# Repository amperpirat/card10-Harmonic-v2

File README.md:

# card10-Harmonic-v2
This is an alternative Harmonic Board for the card10 design.

# Hardware

KiCad version 5.0 or newer is required, 5.1 is recommended.

If you are reading this, you are likely also wondering how to get access to push to this repo.
Currently the repo is read-only, please get in touch directly
via Matrix ( #card10badge:asra.gr ) or IRC ( freenode.com#card10badge, mirror)
if you want to contribute to the hardware.

## Known Issues

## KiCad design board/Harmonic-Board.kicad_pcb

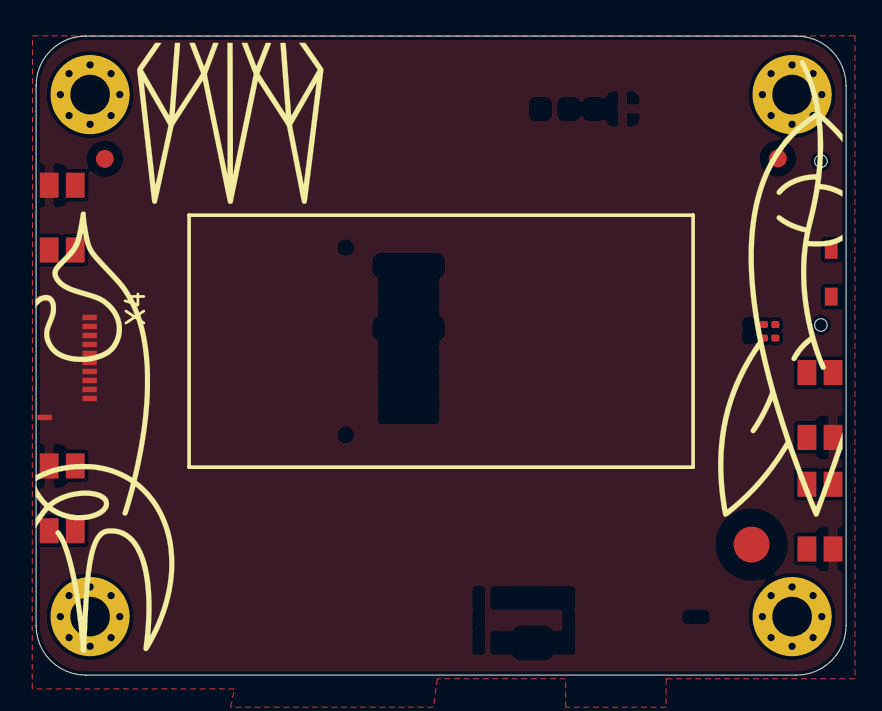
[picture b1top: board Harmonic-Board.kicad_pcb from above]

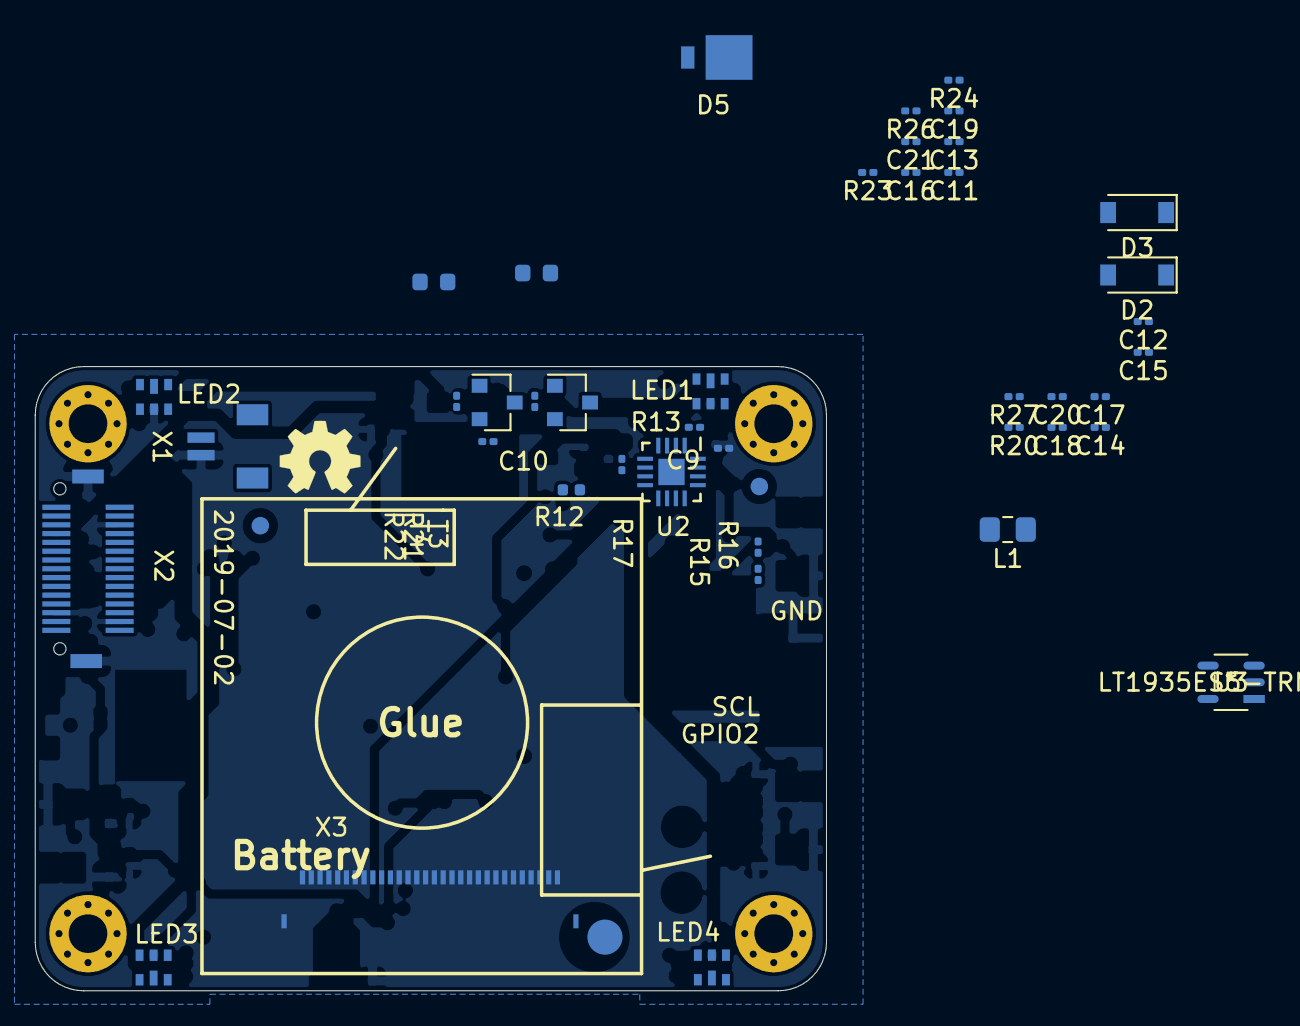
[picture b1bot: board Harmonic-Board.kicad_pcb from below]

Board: 4 copper layers, 45.0 x 35.5 mm, 62 parts (46 on the bottom side), 52 nets, no tracks yet.

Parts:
C9, C10, C11, C14: 100nF; C_0201_0603Metric
C12, C13, C16, C17, C18, C19, C21: 10uF; C_0201_0603Metric
C15: 1uF; C_0201_0603Metric
C20: 330pF; C_0201_0603Metric
D1: SideLED; side-LED
D2, D3: 1N4148; D_SOD-123
D4: IRLED; LED_0603_1608Metric
D5: SS2P6-M3/84A; DO-220AA
FID1, FID2, FID3, FID4, FID5, FID6: Fiducial; Fiducial_1mm_Mask2mm
H1, H4: ECG_VCM; MountingHole_2.2mm_M2_Pad_Via
H2, H3: MountingHole_Pad; MountingHole_2.2mm_M2_Pad_Via
L1: 10uH; L_0805_2012Metric_Pad1.15x1.40mm_HandSolder
LED1, LED2, LED3, LED4: SK9822-2020; SK9822
LOGO1: Logo_Open_Hardware_Large; OSHW-Logo2_7.3x6mm_SilkScreen
LOGO4: Logo_Open_Hardware_Large; artwork-top
R10: 0; R_0201_0603Metric
R11: DNP; R_0201_0603Metric
R12: 10; R_0402_1005Metric
R13, R21, R22: 49.9k; R_0201_0603Metric
R14: 100; R_0603_1608Metric
R15, R16, R17: 4.7k; R_0201_0603Metric
R20, R23: 1M; R_0201_0603Metric
R24: 93,1k; R_0201_0603Metric
R26: 10k; R_0201_0603Metric
R27: 100k; R_0201_0603Metric
SW1, SW2, SW3, SW4: SW_Push; EVQP7J01P
T3, T4: BSS215P; SOT-23
U2: PCAL6408ABS; QFN-16_EP_3x3_Pitch0.5mm
U3: LT1935ES5-TRMPBF
X1: Conn_01x02_Male; SM02B-SRSS-TB
X2: CON_PCB_30pin; 10132797-035100LF
X3: 687130182122
X4: 687106182122; 687110182122

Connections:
+1V8: C9.1, R13.2, U2.15, X2.1, X4.1
+3V3: C10.1, C13.1, C15.1, C17.1, C21.1, D1.2, L1.2, R15.2, R16.2, R17.1, U2.14, U2.16, U3.5, X2.2, X3.4, X3.27, X4.2
+BATT: X1.2, X2.16, X2.17
GND: C9.2, C10.2, C11.1, C12.1, C13.2, C14.2, C15.2, C16.2, C17.2, C18.2, C19.2, C21.2, D3.1, D4.1, LED1.3, LED2.3, LED3.3, LED4.3, R20.1, R26.1, R27.1, SW1.2, SW2.2, SW3.2, SW4.2, U2.6, U3.2, X1.1, X2.4, X2.13, X2.18, X2.29, X2.Tab, X3.1, X3.7, X3.8, X3.9, X3.10, X3.11, X3.15, X3.16, X3.17, X3.18, X3.28, X3.30, X4.6, X4.10
GPIO1: X2.10, X3.20
GPIO2: X2.22, X4.7
GPIO3: R14.2, X2.21
GPIO5: U2.11, X2.11
GPIO6-MISO: X2.25, X4.8
IO-E-P0: R21.2, T3.1, U2.2
IO-E-P1: U2.3, X4.9
IO-E-P2: R22.2, T4.1, U2.4
IO-E-P3: SW3.1, U2.5
IO-E-P4: R17.2, U2.7, X3.21
IO-E-P5: SW1.1, U2.8
IO-E-P6: SW4.1, U2.9
IO-E-P7: R12.1, U2.10
MAX86150_INT: X2.5, X4.3
unnamed: C11.2, X3.26
unnamed: C12.2, X3.3
unnamed: C14.1, C16.1, C18.1, C19.1, C20.2, D5.1, R24.1, X3.2
unnamed: C20.1, R24.2, R26.2, U3.3
unnamed: D1.1, R12.2
unnamed: D2.1, D3.2
unnamed: D2.2, R23.1
unnamed: D4.2, R14.1
unnamed: D5.2, L1.1, U3.1
unnamed: LED1.4, T3.3
unnamed: LED1.5, LED2.2
unnamed: LED1.6, LED2.1
unnamed: LED2.4, LED3.4, LED4.4, T4.3
unnamed: LED2.5, LED3.2
unnamed: LED2.6, LED3.1
unnamed: LED3.5, LED4.2
unnamed: LED3.6, LED4.1
unnamed: R10.2, X2.14
unnamed: R11.2, X2.15
unnamed: R13.1, U2.1
unnamed: R20.2, X3.22
unnamed: R23.2, X3.5
unnamed: R27.2, U3.4
PMIC_nEN: SW2.1, X2.19
RGB_LED_CLK: LED1.2, X2.8
RGB_LED_Data: LED1.1, X2.9
SCL_1V8: U2.12, X2.7, X4.5
SCL_3V3: R16.1, X2.12
SDA_1V8: U2.13, X2.6, X4.4
SDA_3V3: R15.1, X2.28
SPI_CS: X2.23, X3.19
SPI_MOSI: X2.24, X3.13
SPI_SCK: X2.26, X3.14
VSYS: R21.1, R22.1, T3.2, T4.2, X2.3

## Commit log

2021-08-04 added project files
2021-08-04 added part lib for LT1935 footprint
2021-08-04 added part lib for LT1935 schematic symbol
2021-08-04 worked on schematics: - added new display - delete unwanted parts
    Work on PCB:
    - cleaned old pcb routes
2021-08-06 - Added connector lib - added footprint for schottkey diode - added keep-out for new display
2021-08-06 - added lib for display and add-on connector

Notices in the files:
parts and their libraries:
Copyright 2021 Accelerated Designs. All rights reserved.
